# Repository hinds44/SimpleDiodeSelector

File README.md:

# SimpleDiodeSelector
Simple PCB to allow user to select between pairs of clipping diodes

Wire IN and OUT of X1 to the circuit, replacing a pair of clipping diodes, then use a [2-pin jumper](https://mou.sr/3IZE1Zd) to select which diode pair to use. 

![alt text][selectorImage]

[selectorImage]: https://github.com/hinds44/SimpleDiodeSelector/blob/main/SimpleDiodeSelector/SimpleDiodeSelector.png "The Diode Selector"

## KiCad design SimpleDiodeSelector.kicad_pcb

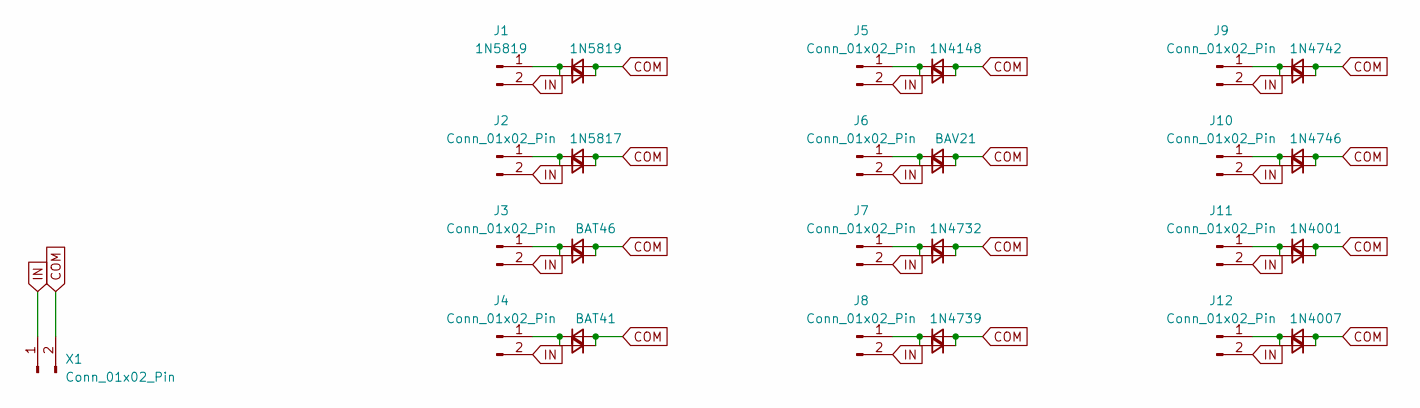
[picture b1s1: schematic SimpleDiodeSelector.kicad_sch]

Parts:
D1: 1N5819; D_DO-41_SOD81_P7.62mm_Horizontal
D2, D4, D14, D16, D18, D20, D22, D24: D_Small; D_DO-41_SOD81_P7.62mm_Horizontal
D3: 1N5817; D_DO-41_SOD81_P7.62mm_Horizontal
D5: BAT46; D_DO-35_SOD27_P7.62mm_Horizontal
D6, D12: D_Small; D_DO-35_SOD27_P7.62mm_Horizontal
D7: BAT41; D_DO-34_SOD68_P7.62mm_Horizontal
D8, D10: D_Small; D_DO-34_SOD68_P7.62mm_Horizontal
D9: 1N4148; D_DO-34_SOD68_P7.62mm_Horizontal
D11: BAV21; D_DO-35_SOD27_P7.62mm_Horizontal
D13: 1N4732; D_DO-41_SOD81_P7.62mm_Horizontal
D15: 1N4739; D_DO-41_SOD81_P7.62mm_Horizontal
D17: 1N4742; D_DO-41_SOD81_P7.62mm_Horizontal
D19: 1N4746; D_DO-41_SOD81_P7.62mm_Horizontal
D21: 1N4001; D_DO-41_SOD81_P7.62mm_Horizontal
D23: 1N4007; D_DO-41_SOD81_P7.62mm_Horizontal
J1: 1N5819; PinHeader_1x02_P2.54mm_Vertical
J2, J3, J4, J5, J6, J7, J8, J9, J10, J11, J12: Conn_01x02_Pin; PinHeader_1x02_P2.54mm_Vertical
X1: Conn_01x02_Pin; 1x02_Wire_P5.08

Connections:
COM: D1.2 (A), D2.1 (K), D3.2 (A), D4.1 (K), D5.2 (A), D6.1 (K), D7.2 (A), D8.1 (K), D9.2 (A), D10.1 (K), D11.2 (A), D12.1 (K), D13.2 (A), D14.1 (K), D15.2 (A), D16.1 (K), D17.2 (A), D18.1 (K), D19.2 (A), D20.1 (K), D21.2 (A), D22.1 (K), D23.2 (A), D24.1 (K), X1.2
IN: J1.2, J2.2, J3.2, J4.2, J5.2, J6.2, J7.2, J8.2, J9.2, J10.2, J11.2, J12.2, X1.1
unnamed: D1.1 (K), D2.2 (A), J1.1
unnamed: D3.1 (K), D4.2 (A), J2.1
unnamed: D5.1 (K), D6.2 (A), J3.1
unnamed: D7.1 (K), D8.2 (A), J4.1
unnamed: D9.1 (K), D10.2 (A), J5.1
unnamed: D11.1 (K), D12.2 (A), J6.1
unnamed: D13.1 (K), D14.2 (A), J7.1
unnamed: D15.1 (K), D16.2 (A), J8.1
unnamed: D17.1 (K), D18.2 (A), J9.1
unnamed: D19.1 (K), D20.2 (A), J10.1
unnamed: D21.1 (K), D22.2 (A), J11.1
unnamed: D23.1 (K), D24.2 (A), J12.1

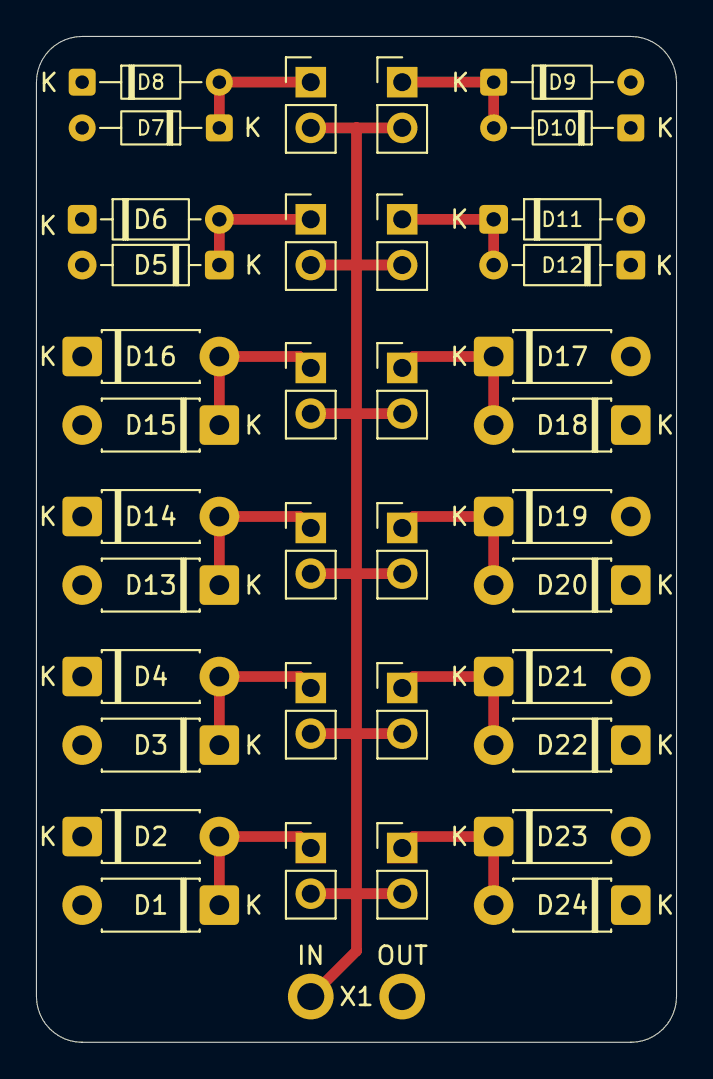
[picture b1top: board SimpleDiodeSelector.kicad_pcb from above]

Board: 2 copper layers, 35.6 x 55.9 mm, 37 parts (0 on the bottom side), 14 nets.

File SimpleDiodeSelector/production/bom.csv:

Designator,Footprint,Quantity,Value,LCSC Part #
D1,D_DO-41_SOD81_P7.62mm_Horizontal,1,1N5819,
"D10, D8",D_DO-34_SOD68_P7.62mm_Horizontal,2,D_Small,
D11,D_DO-35_SOD27_P7.62mm_Horizontal,1,BAV21,
"D12, D6",D_DO-35_SOD27_P7.62mm_Horizontal,2,D_Small,
D13,D_DO-41_SOD81_P7.62mm_Horizontal,1,1N4732,
"D14, D16, D18, D2, D20, D22, D24, D4",D_DO-41_SOD81_P7.62mm_Horizontal,8,D_Small,
D15,D_DO-41_SOD81_P7.62mm_Horizontal,1,1N4739,
D17,D_DO-41_SOD81_P7.62mm_Horizontal,1,1N4742,
D19,D_DO-41_SOD81_P7.62mm_Horizontal,1,1N4746,
D21,D_DO-41_SOD81_P7.62mm_Horizontal,1,1N4001,
D23,D_DO-41_SOD81_P7.62mm_Horizontal,1,1N4007,
D3,D_DO-41_SOD81_P7.62mm_Horizontal,1,1N5817,
D5,D_DO-35_SOD27_P7.62mm_Horizontal,1,BAT46,
D7,D_DO-34_SOD68_P7.62mm_Horizontal,1,BAT41,
D9,D_DO-34_SOD68_P7.62mm_Horizontal,1,1N4148,
J1,PinHeader_1x02_P2.54mm_Vertical,1,1N5819,
"J10, J11, J12, J2, J3, J4, J5, J6, J7, J8, J9",PinHeader_1x02_P2.54mm_Vertical,11,Conn_01x02_Pin,
X1,1x02_Wire_P5.08,1,Conn_01x02_Pin,

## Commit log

2025-08-01 initialize to existing files
2025-08-01 image of PCB
2025-08-01 remove duplicates
2025-08-01 added image
2025-08-04 Create LICENSE
2025-08-04 add image to README.md
2025-08-04 changed
